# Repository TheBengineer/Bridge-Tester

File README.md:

Bridge-Tester
=============

An Open Source bridge tester for popsicle stick bridge competitions.

This was my senior project at Vermont Technical College along with [Carter](
https://github.com/R8driver)

We designed this bridge crusher to be able to crush bridges of up to one meter long, while measuring characturistics about their weight.

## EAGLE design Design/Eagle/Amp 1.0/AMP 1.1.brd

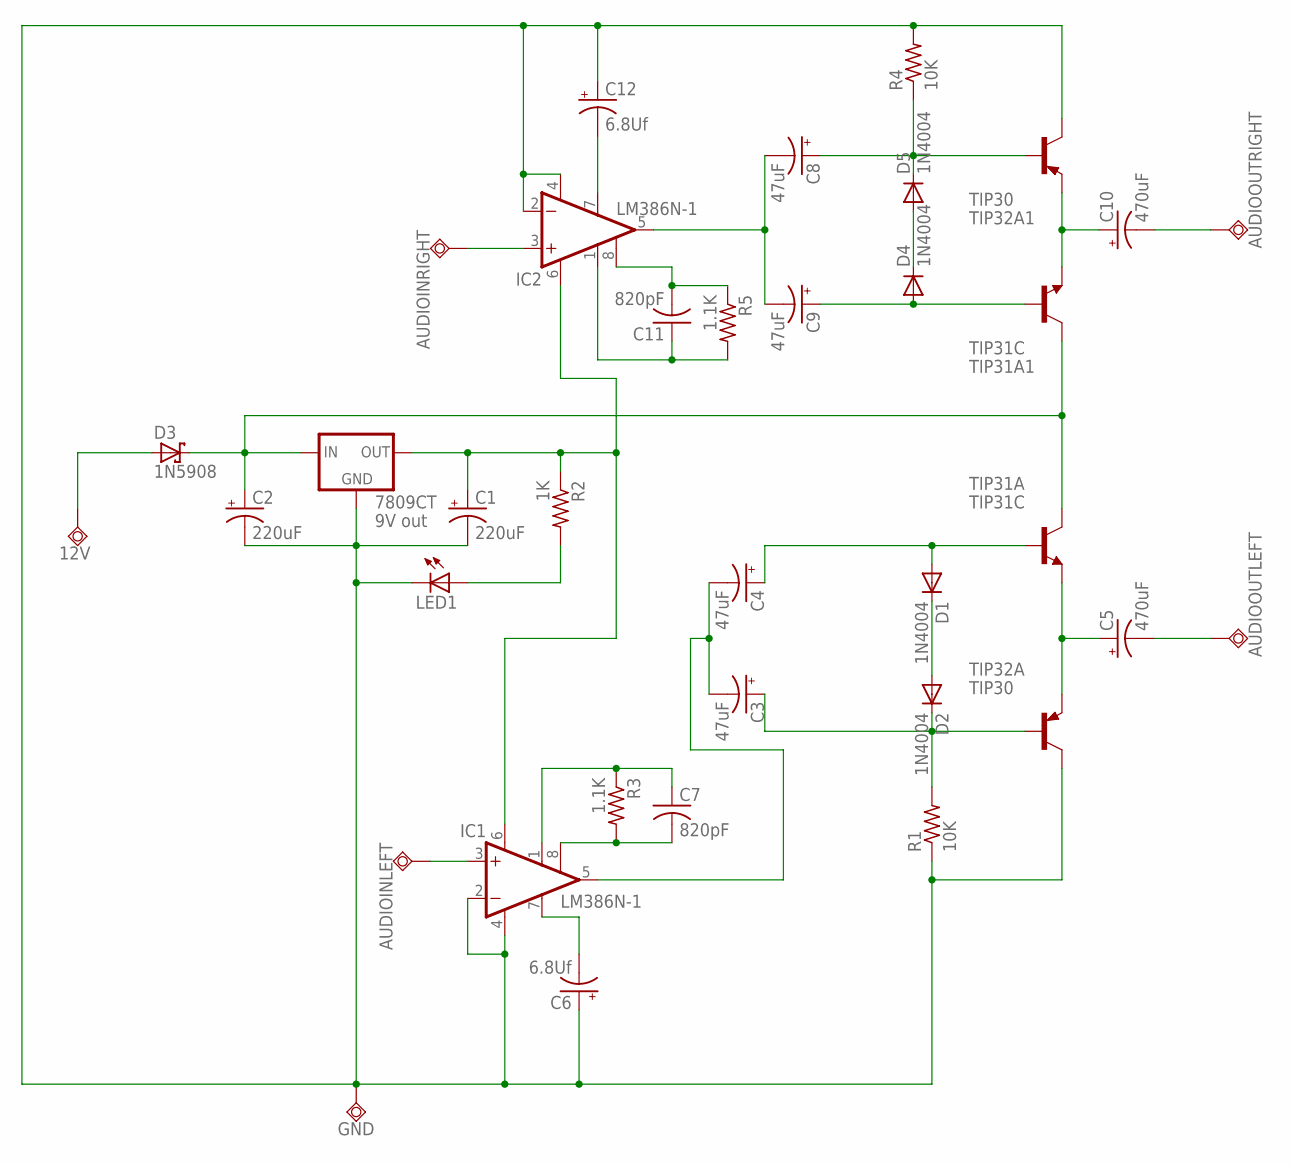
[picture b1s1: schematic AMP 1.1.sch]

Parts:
12V: TPSQPAD1-20; P1-20
7809CT: 9V out; 78XXL
AUDIOINLEFT: TPSQPAD1-20; P1-20
AUDIOINRIGHT: TPSQPAD1-20; P1-20
AUDIOOUTLEFT: TPSQPAD1-20; P1-20
AUDIOOUTRIGHT: TPSQPAD1-20; P1-20
C1, C2: 220uF; B45181C
C3, C4, C8, C9: 47uF; E5-4
C5, C10: 470uF; E5-4
C6, C12: 6.8Uf; E5-4
C7, C11: 820pF; C050-050X075
D1, D2, D4, D5: 1N4004; DO41-10
D3: 1N5908; C4111-15
GND: TPSQPAD1-20; P1-20
IC1, IC2: LM386N-1; DIL08
LED1: LED5MM
R1, R4: 10K; 0204/7
R2: 1K; 0204/7
R3, R5: 1.1K; 0204/7
TIP31A, TIP31A1: TIP31C; TO220
TIP32A, TIP32A1: TIP30; TO220

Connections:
unnamed: D1.C, D2.A
unnamed: C3.+, D2.C, R1.2, TIP32A.1 (B)
unnamed: C4.+, D1.A, TIP31A.1 (B)
unnamed: C5.+, TIP31A.3 (E), TIP32A.3 (E)
unnamed: AUDIOOUTLEFT.TP, C5.-
unnamed: 7809CT.IN, C2.+, D3.C, TIP31A.2 (C), TIP31A1.2 (C)
unnamed: AUDIOINLEFT.TP, IC1.3 (+IN)
unnamed: 7809CT.OUT, C1.+, IC1.6 (VS), IC2.6 (VS), R2.1
unnamed: C3.-, C4.-, IC1.5 (OUT)
unnamed: LED1.A, R2.2
unnamed: 12V.TP, D3.A
unnamed: C6.-, IC1.7 (BYPASS)
unnamed: C7.2, IC1.8 (GAIN), R3.2
unnamed: AUDIOINRIGHT.TP, IC2.3 (+IN)
unnamed: C7.1, IC1.1 (GAIN), R3.1
unnamed: C10.+, TIP31A1.3 (E), TIP32A1.3 (E)
unnamed: C8.+, D5.C, R4.1, TIP32A1.1 (B)
unnamed: C9.+, D4.A, TIP31A1.1 (B)
unnamed: D4.C, D5.A
unnamed: AUDIOOUTRIGHT.TP, C10.-
unnamed: C8.-, C9.-, IC2.5 (OUT)
unnamed: 7809CT.GND, C1.-, C2.-, C6.+, C12.+, GND.TP, IC1.2 (-IN), IC1.4 (GND), IC2.2 (-IN), IC2.4 (GND), LED1.K (C), R1.1, R4.2, TIP32A.2 (C), TIP32A1.2 (C)
unnamed: C11.2, IC2.8 (GAIN), R5.1
unnamed: C11.1, IC2.1 (GAIN), R5.2
unnamed: C12.-, IC2.7 (BYPASS)

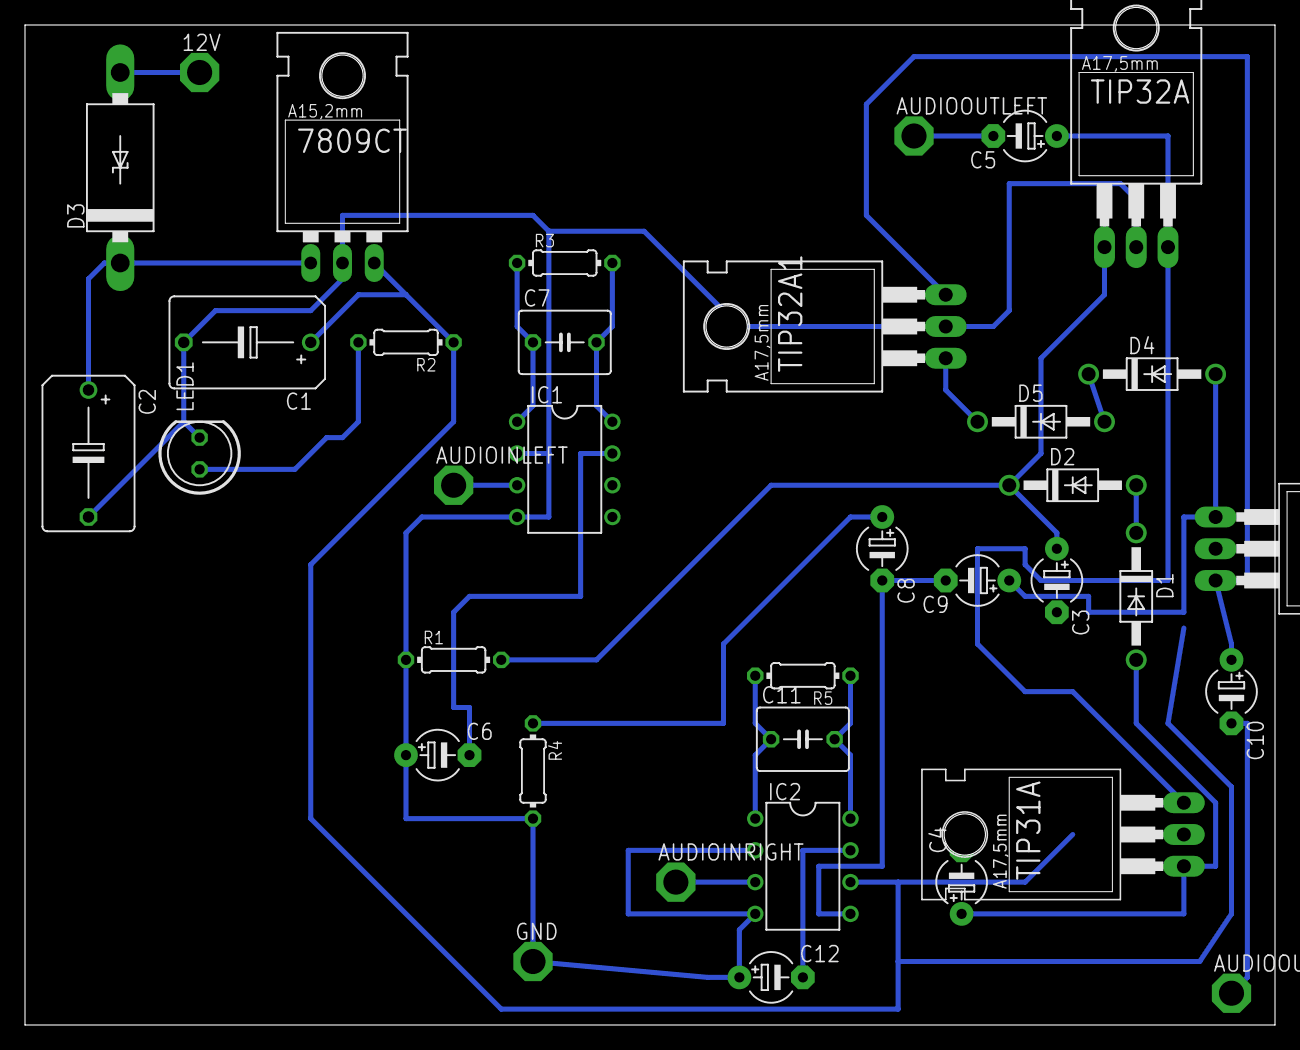
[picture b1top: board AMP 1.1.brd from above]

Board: 2 copper layers, 100.0 x 80.0 mm, 36 parts (0 on the bottom side), 25 nets.

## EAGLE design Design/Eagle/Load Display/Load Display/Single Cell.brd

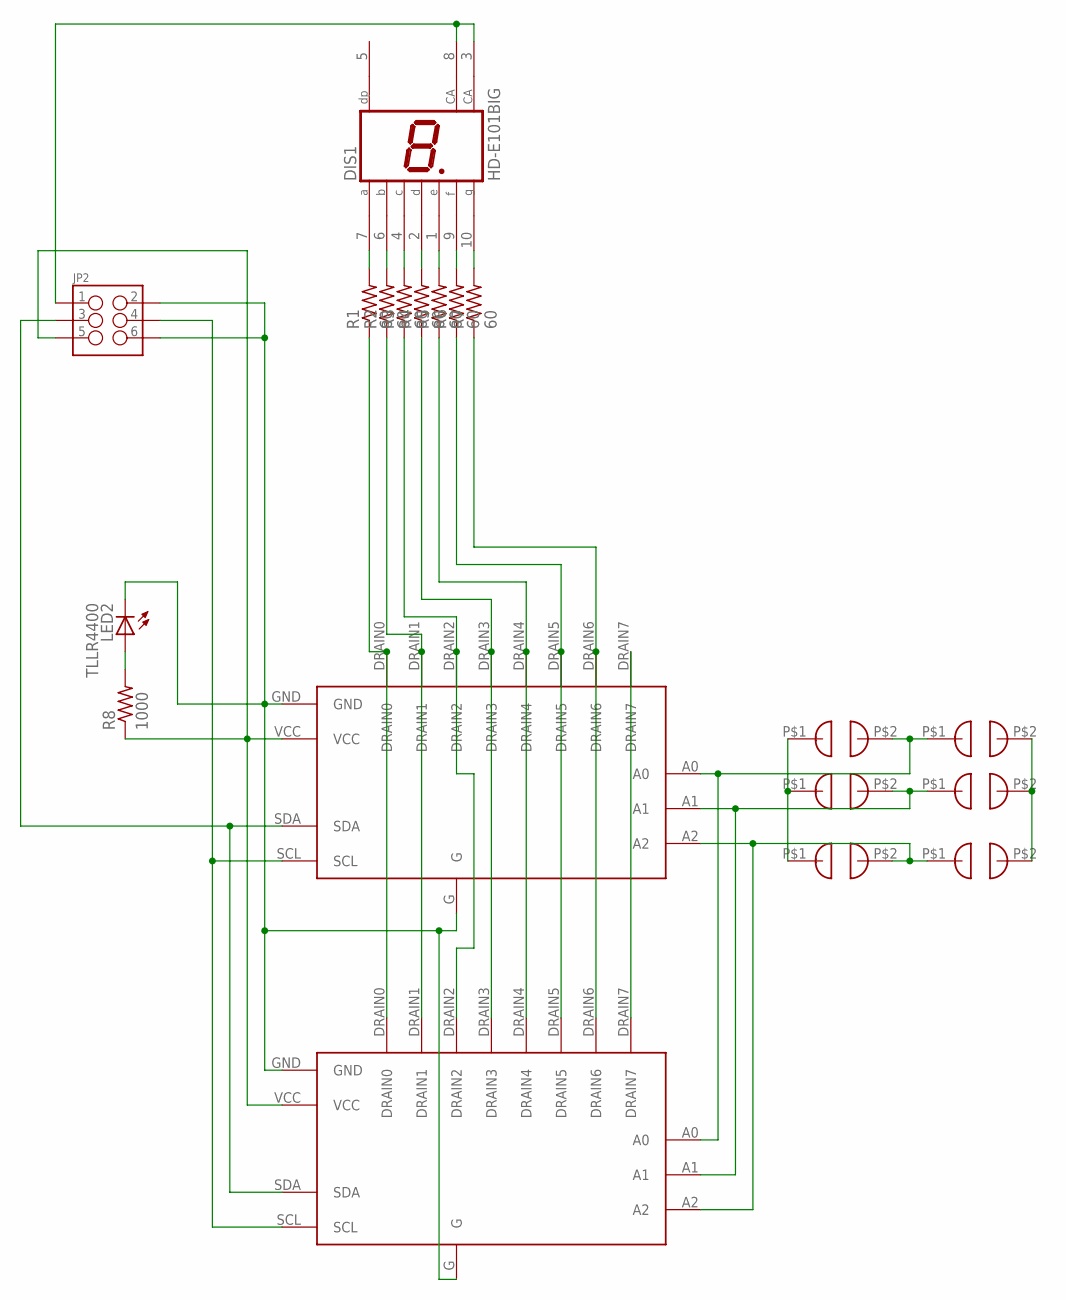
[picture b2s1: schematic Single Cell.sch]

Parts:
DIS1: HD-E101BIG; 7SEGMENT_BACKWARDS
JP2: M03X2SHROUD; 2X3-SHROUDED
LED2: TLLR4400; LED3MM
R1, R2, R3, R4, R5, R6, R7: 60; 0207/15
R8: 1000; 0207/15
U$1, U$3, U$4, U$5, U$6, U$7: SOLDER_JUMPER
U$2: LED_DRIVERBOARDADAFRUIT; DRIVER_BOARD_ADAFRUIT
U$8: LED_DRIVERBOARD; DRIVER_BOARD

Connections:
GND: JP2.2, JP2.6, LED2.K (C), U$1.P$1, U$2.G, U$2.GND, U$4.P$1, U$6.P$1, U$8.G, U$8.GND
unnamed: DIS1.7 (A), R1.2
unnamed: DIS1.6 (B), R2.2
unnamed: DIS1.4 (C), R3.2
unnamed: DIS1.2 (D), R4.2
unnamed: DIS1.1 (E), R5.2
unnamed: DIS1.9 (F), R6.2
unnamed: DIS1.10 (G), R7.2
unnamed: R1.1, U$2.DRAIN0, U$8.DRAIN0
unnamed: R2.1, U$2.DRAIN1, U$8.DRAIN1
unnamed: R3.1, U$2.DRAIN2, U$8.DRAIN2
unnamed: R4.1, U$2.DRAIN3, U$8.DRAIN3
unnamed: R5.1, U$2.DRAIN4, U$8.DRAIN4
unnamed: R6.1, U$2.DRAIN5, U$8.DRAIN5
unnamed: R7.1, U$2.DRAIN6, U$8.DRAIN6
unnamed: U$2.A1, U$4.P$2, U$5.P$1, U$8.A1
unnamed: U$2.A2, U$6.P$2, U$7.P$1, U$8.A2
unnamed: U$2.DRAIN7, U$8.DRAIN7
unnamed: LED2.A, R8.2
unnamed: U$1.P$2, U$2.A0, U$3.P$1, U$8.A0
SDA: JP2.3, U$2.SDA, U$8.SDA
SSCL: JP2.4, U$2.SCL, U$8.SCL
VCC5: JP2.5, R8.1, U$2.VCC, U$3.P$2, U$5.P$2, U$7.P$2, U$8.VCC
VCC12: DIS1.3 (CA), DIS1.8 (CA), JP2.1

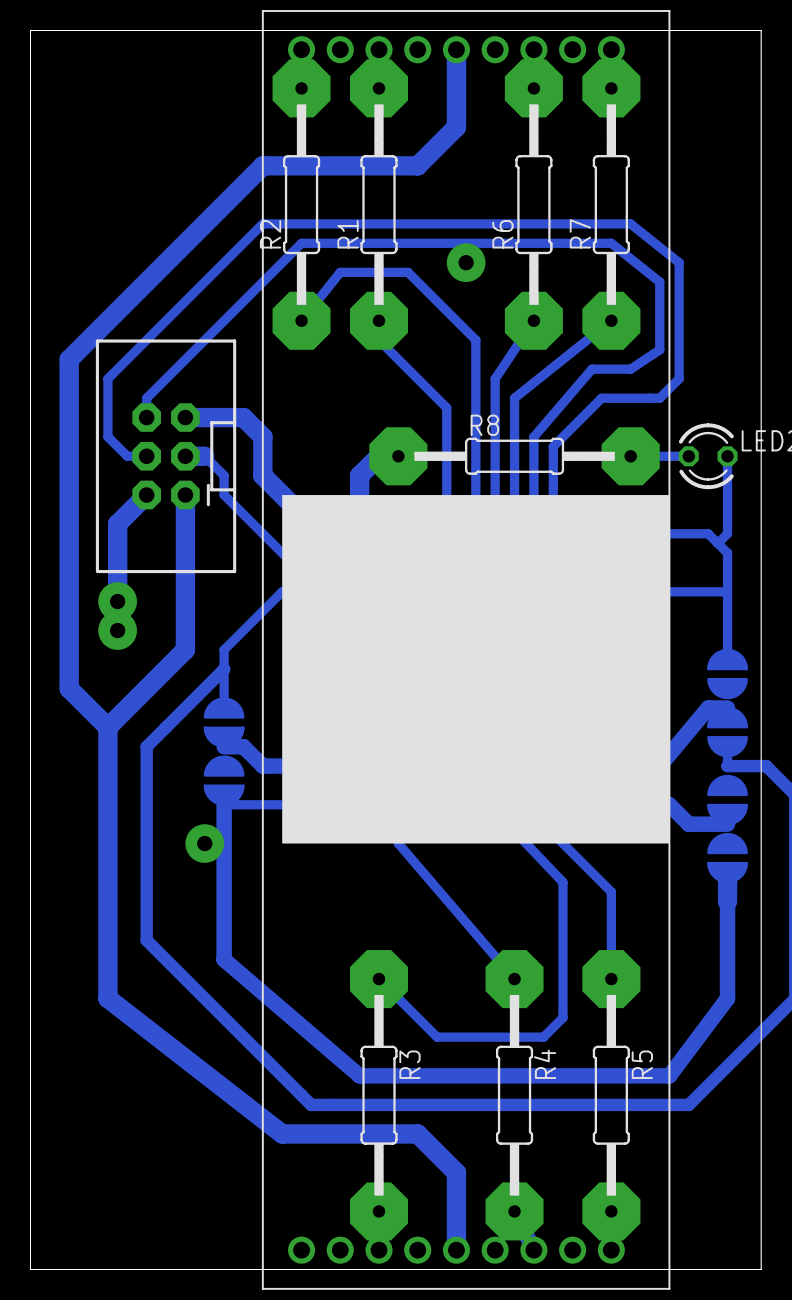
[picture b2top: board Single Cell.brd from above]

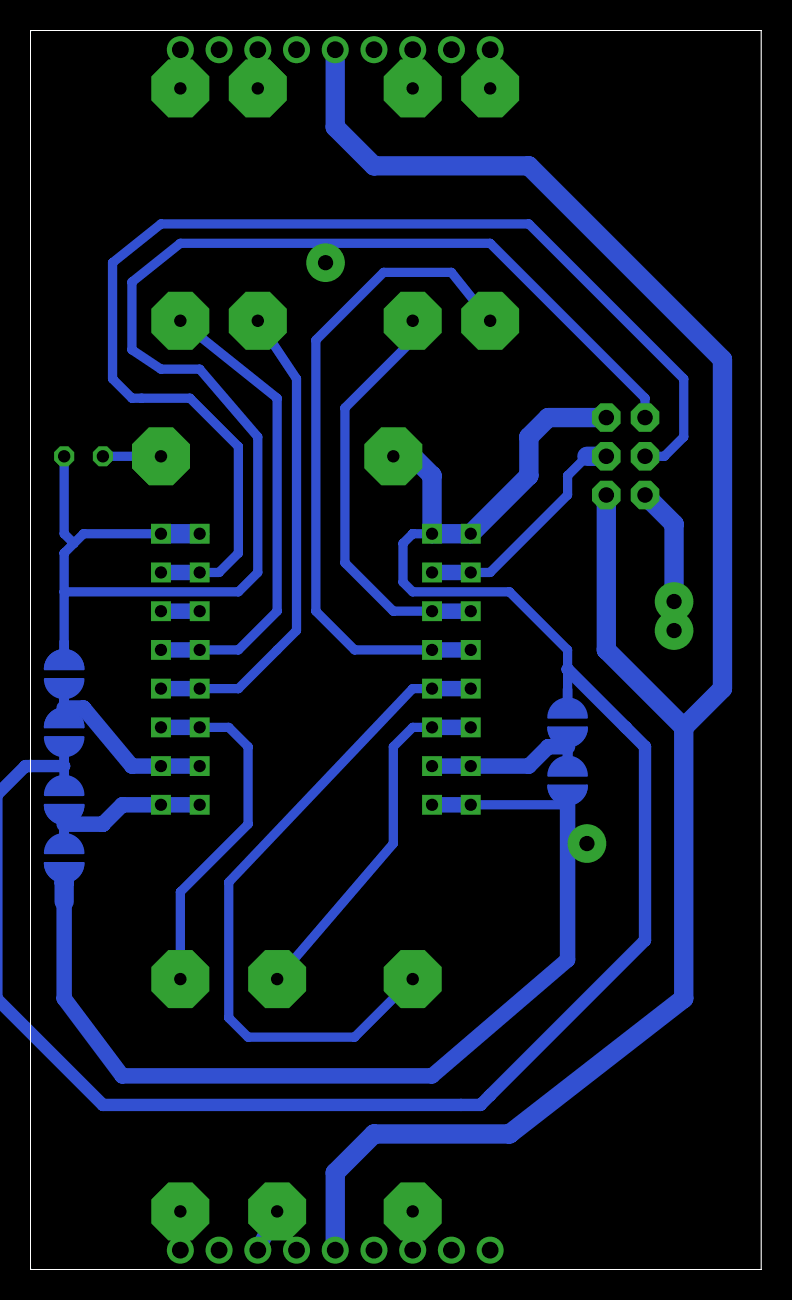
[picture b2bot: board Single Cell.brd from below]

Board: 2 copper layers, 47.9 x 81.3 mm, 19 parts (6 on the bottom side), 24 nets.

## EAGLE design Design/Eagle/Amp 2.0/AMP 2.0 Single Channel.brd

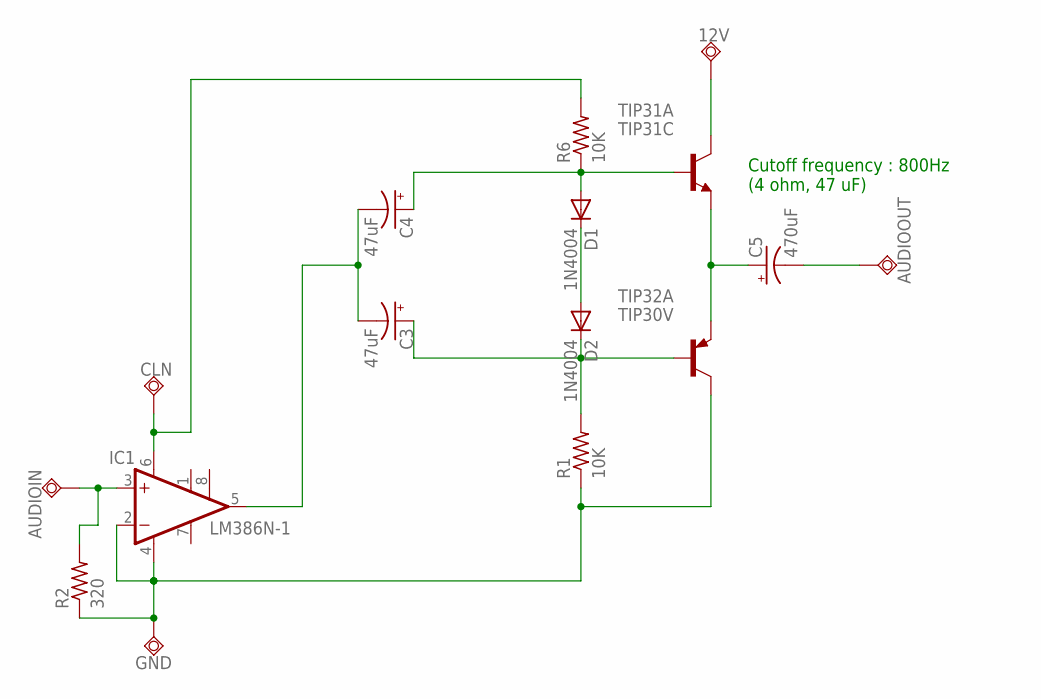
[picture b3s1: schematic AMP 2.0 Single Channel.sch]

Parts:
12V: TPSQPAD1-20; P1-20
AUDIOIN: TPSQPAD1-20; P1-20
AUDIOOUT: TPSQPAD1-20; P1-20
C3, C4: 47uF; E5-4
C5: 470uF; E5-4
CLN: TPSQPAD1-20; P1-20
D1, D2: 1N4004; DO41-10
GND: TPSQPAD1-20; P1-20
IC1: LM386N-1; DIL08
R1, R6: 10K; 0204/7
R2: 320; 0204/7
TIP31A: TIP31C; TO220V
TIP32A: TIP30V; TO220V

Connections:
AALFT: C3.-, C4.-, IC1.5 (OUT)
ALFT: AUDIOIN.TP, IC1.3 (+IN), R2.2
AULEFT: AUDIOOUT.TP, C5.-
CLEANPWR: C4.+, D1.A, R6.1, TIP31A.1 (B)
GND: GND.TP, IC1.2 (-IN), IC1.4 (GND), R1.1, R2.1, TIP32A.2 (C)
unnamed: D1.C, D2.A
unnamed: C3.+, D2.C, R1.2, TIP32A.1 (B)
unnamed: CLN.TP, IC1.6 (VS), R6.2
unnamed: C5.+, TIP31A.3 (E), TIP32A.3 (E)
unnamed: 12V.TP, TIP31A.2 (C)

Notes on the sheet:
Cutoff frequency : 800Hz (4 ohm, 47 uF)

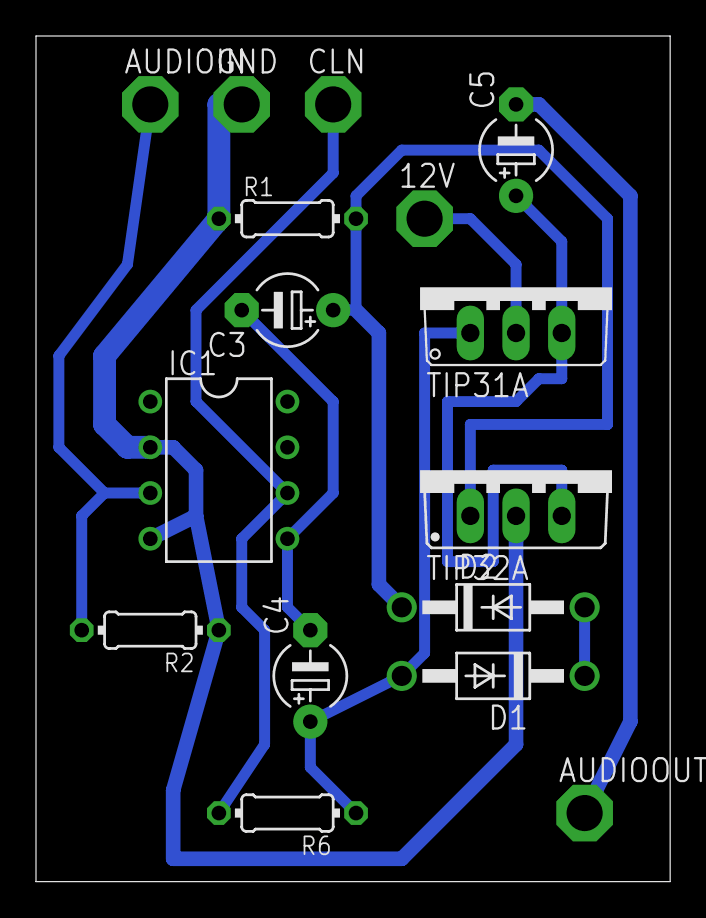
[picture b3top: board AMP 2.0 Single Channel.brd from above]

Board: 2 copper layers, 35.2 x 47.0 mm, 16 parts (0 on the bottom side), 10 nets.

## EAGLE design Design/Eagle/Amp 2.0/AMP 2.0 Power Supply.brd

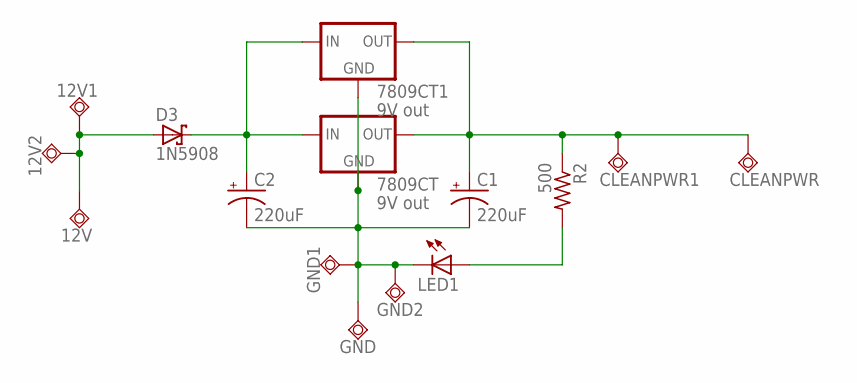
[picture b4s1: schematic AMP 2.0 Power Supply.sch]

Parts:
12V, 12V1, 12V2: TPSQPAD1-20; P1-20
7809CT, 7809CT1: 9V out; 78XXS
C1, C2: 220uF; B45181C
CLEANPWR, CLEANPWR1: TPSQPAD1-20; P1-20
D3: 1N5908; C4111-15
GND, GND1, GND2: TPSQPAD1-20; P1-20
LED1: LED5MM
R2: 500; 0204/7

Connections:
BUFFEREDDIRTY: 7809CT.IN, 7809CT1.IN, C2.+, D3.C
CLEAN9V: 7809CT.OUT, 7809CT1.OUT, C1.+, CLEANPWR.TP, CLEANPWR1.TP, R2.1
unnamed: 7809CT.GND, 7809CT1.GND, C1.-, C2.-, GND.TP, GND1.TP, GND2.TP, LED1.K (C)
unnamed: 12V.TP, 12V1.TP, 12V2.TP, D3.A
unnamed: LED1.A, R2.2

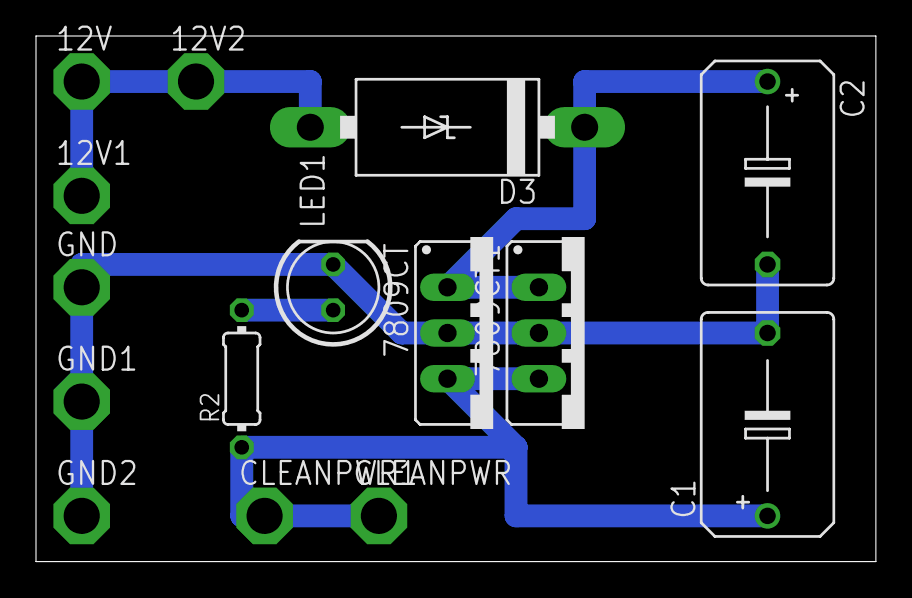
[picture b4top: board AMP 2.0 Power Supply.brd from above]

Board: 2 copper layers, 46.7 x 29.2 mm, 15 parts (0 on the bottom side), 5 nets.

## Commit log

2013-11-06 Working on the preliminary presentation
2013-11-06 Added the latest Version of the powerpoint.
2013-11-06 Final Version
    Presented today, went well.
2013-11-06 Final Version
    Presented Today
2013-11-11 Added a Bill Of Materials.
2013-11-12 Updated the BOM to include categories and a pie chart. Waiting on links.
2013-11-13 Added some Solidworks models
2013-11-20 Added a powerpoint for GPIO pins on the RPi
2013-11-20 Not sure what this is
2013-11-20 Added some stuff to the BOM
2013-11-20 Updated BOM
    Added Rasberry Pi, Monitor, and pressure sensor.
2013-12-09 See Extended
    Added to BOM
    Added a bunch of stuff for the presentation
2013-12-11 Small tweaking needed, and Notes
2013-12-11 Final Wording. Needs Notes
2013-12-11 Added the notes to the presentation
2014-01-13 Made a Solidworks model of the frame. new Folder structure
2014-01-20 Added some stuff
2014-01-22 Worked on the frame. Optimized frame. Bom updated
2014-01-22 Moved files around.
2014-01-22 Added a folder for subsystems. Started work on transcribing the hydraulic subsystem diagram from my notebook to Powerpoint.
2014-01-23 Made Hydraulic symbols
2014-01-23 Finished Hydraulic Design Updated BOM.xlsx with new parts
2014-01-23 Figured out the fittings
2014-01-25 Updated the BOM.xlsx Started on a Force Sensor Diagram
2014-01-25 Finished System Diagram
2014-01-25 Test
2014-01-28 Added a filter to the Hydraulic.pptx Design added a steel BOM.txt converted the frame reports to PDF. Deleted the extra Solidworks folder. (Some files are still read only and I can't delete them.)
2014-01-28 Added steel lists to the bom.
2014-01-28 Updated the BOM. Deleted the extra solidworks folder
2014-01-28 Updated BOM to have shipping Updated hydraulics to include filter
2014-02-03 Updated BOM.xlsx
    Did some statics on the Plate to see how strong it is.
2014-02-08 Found couplings for motor and pump. Unsure of pump keyway size, so got the larger option. Added Thumbs.db to the .gitignore file.
2014-02-09 Updated the BOM: Added 7 segments Added a i2d driver for 7 segments Sorted by who should order
    Working on presentation. Needs a lot of work.
2014-02-09 Made a page on the BOM for the presentation. (Removed links and shrunk the page) Presentation is done except for the electrical slide.
2014-02-09 Added an eagle directory. Added a custom eagle library for the 4" 7 segment and the I2C driver Added a project for the Load Display
2014-02-10 Added some eagle files
2014-02-10 Presentation needs notes
2014-02-10 Added a 5V regulator
2014-02-10 Latest presentation
2014-02-10 Added a spreadsheet with stuff to order.
2014-02-10 Final version of presentation. Need to add feedback.
2014-02-13 Broke the BOM into individual files for Bob and Geoff to order stuff
2014-02-13 Updated Steel list
2014-02-25 LED is blinking on the A side.
2014-02-25 Added a lot of eagle stuff
2014-02-25 IIC drivers do not work the way i want the too.
2014-03-11 Did a lot of work
2014-03-20 Added a bunch of eagle files. Working on PowerPoint
2014-03-20 Working on the presentation.
2014-03-20 Adding the load display subsystem diagram
2014-03-24 Modified the bracket file. Added the presentation.
2014-03-24 Added the 7 segment boards
2014-03-28 Added all the python scripts for the GUI
2014-04-03 Added a bunch of local files
2014-04-04 Added a bunch of stuff to make the new 7 segment boards.
2014-04-08 Added the python program Carter Wrote
2014-04-08 Fixed some errors on the IIC section of the master file.
2014-04-08 Working on some code with Carter
2014-04-08 Finished the board for the 7 segments.
2014-04-08 Closed eagle.
2014-04-08 Merge remote-tracking branch 'remotes/origin/Panic_Mode_Ben' into HEAD
    Conflicts:
    Python/Master.py
2014-04-08 Polished the presentation, and renamed the folder.
2014-04-10 Changed the eagle board to run the 5v in a better path.
2014-04-14 Changed the distance address to the pressure address for testing and fixed bugs.
2014-04-14 Working on making the sortware work. Have decided to ignore the 7 segments for now.
2014-04-14 Attempting to save github password
2014-04-14 working on data structures
2014-04-14 fleshing out the Python program
2014-04-15 Code is working kinda sorta. Need to polish, and all kinds of stufff, but it works. Even te graph.
2014-04-15 Files were hiding
2014-04-15 Graphing works, and autoscales automatically.
2014-04-15 Software graphs propperly in the vertical axis.
2014-04-15 Scalling is off, but the graph works really well. also, noise is minimal.
2014-04-15 Found the bug. Was adding 1 to the max data, but often the data was really small. Fixed
2014-04-15 Having the program display raw ADC values, so I can calibrate
2014-04-15 Graph is working. having troulbe with calibrating the force
2014-04-15 Switching to Master
2014-04-16 Latest version of the software. has gain built in.
2014-04-16 Added a tag to display the peak point. Need to add some polishing there.
2014-04-16 Tag text is working. Do want to make the tag switch sides
2014-04-16 Draw Graph functuion is just about finshed. Do want to impliment not drawing every frame.
2014-04-16 Graph is working. Fullscreen is working. Needs some better averaging. NOT ENOUGH FPS
2014-04-16 Trying with fullscreen 1024x768. About the smallest size I think is reasonable. (Wrong aspect ratio)
2014-04-16 Changed res to 16:9 1024:576
2014-04-16 Fixed error
2014-04-16 stopped drawing the background
2014-04-16 poling thread had no limit. Fixed
2014-04-16 latest
2014-04-17 Found out that it was adding every sample, now using 10x averaging. Also, 500 lines = ~.065 seconds to draw, so is about max
2014-04-17 working on optimizing the draw chart function
2014-04-17 sset line width to 1. 150% speed boost.
2014-04-17 Graph is working, forking for calibration run.
2014-04-17 forkeed to do calibation
2014-04-17 distance poling removed. should get good speed.
2014-04-17 averaging set to 50x
2014-04-17 Calibration ready, but there is a lot of noise.
2014-04-17 87 lb of noise. thats bad.
2014-04-17 ready for calibration. Unfortunatly, there is a lot of load noise. about 30lb's worth.
2014-04-17 Set up for calibating. seems tobe working well.
2014-04-17 Pi crashed due to vibrations on HDD. I/O error
2014-04-17 PGA had some wierd settings. Is now limited.
2014-04-18 Calibration data added
2014-04-18 Working on formating the load string. Also need to add calibration values.
2014-04-18 Calibration added, but it doeesn't work
2014-04-18 Calibration is failig sanity check. Probably not catching the peak.
2014-04-18 Ran program,and times changed
2014-04-18 Gains are now working propperly.
2014-04-18 calibration works now. for some reason
2014-04-18 New calibration numbers
2014-04-18 Brought the tags out into a functtion
2014-04-18 Working on UI
2014-04-18 added the over limit sound
2014-04-19 Shiney
2014-04-19 UI is good. removing gains
2014-04-19 Broken.
2014-04-19 Still broken when a reset is called
2014-04-19 Added some files. Program works so far.
2014-04-19 sofware is almost done
2014-04-21 Moved the redraw around. may need to bring back the old code for the deflection. NOTE on windows, the text is in the wrong location.
2014-04-21 Graphs was overrighting.
2014-04-21 Drawing effort is minimized. Might precompute all the boardder drwings, but that isn't too important.
2014-04-21 Added the dedication stuff. need some text. Add a picture?
2014-04-21 Added the dedication
2014-04-22 Lost some commits because GIT. Moving draw chart out of it's function. Also optimizing
2014-04-22 Boarder is ddrawing. working on the scaling code
2014-04-22 Boken. moving the ddraw chart function to inline code.
2014-04-22 Puller is working. Needs polishing and distance added
2014-04-22 Adding a average line next to the max line
2014-04-22 Average now draws as blue. Will discuss withCarter what works best.
2014-04-23 Load graph is basically done. Need to switch over to average.
2014-04-23 Averaging wa not being done propperly
2014-04-23 Software is working great. Might add scales on graphs
2014-04-24 Added an auto scaling axis to the graph. Need to check for performance.
2014-04-24 Graph is finished an polished. Axises are metered, bit not labeled.
2014-04-24 Added shutdown message to escape
2014-04-24 Added Q to quit without shutdown.
2014-04-24 Added Full screen back in.
2014-04-24 Software is "Done"
2014-04-25 Added a key for the dedication "D"
2014-04-25 Fixed indintation
2014-04-26 Hid mouse Cursor
2014-04-27 Added the final presentation, and a schematic of the Main board
2014-05-06 Uncommented the dedication
2014-05-06 Added the keey presses for the control box
2014-05-06 Working on flash drive backup
2014-05-06 Removed fullscreen for debug mode
2014-05-06 saving to flash drive might be done.
2014-05-06 Saving to flash drive works.
2014-05-06 set back to fullscreen. should be working.
2014-05-06 Found a but if the flashdrive is not in place.
2014-05-06 Fullscreen
2014-05-06 Volume rocker works, fullscreen
2014-11-21 Added the website to the README
2014-12-05 Added an image for the screenshot
2014-12-05 Added a header image
2017-01-27 Retrofitting a USB sensor in.
2017-01-27 Added a USB reader.
2017-01-27 Working on adding the USB sensor back in.
2017-01-27 Different way of detecting i2c
2017-01-27 Extra io error
2017-01-27 Catch None
2017-01-27 Added a break
2017-01-27 asdf
2017-01-27 adsf

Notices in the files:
parts and their libraries:
Ben-SF-Con: Licensing: CC v3.0 Share-Alike You are welcome to use this library for commercial purposes.
